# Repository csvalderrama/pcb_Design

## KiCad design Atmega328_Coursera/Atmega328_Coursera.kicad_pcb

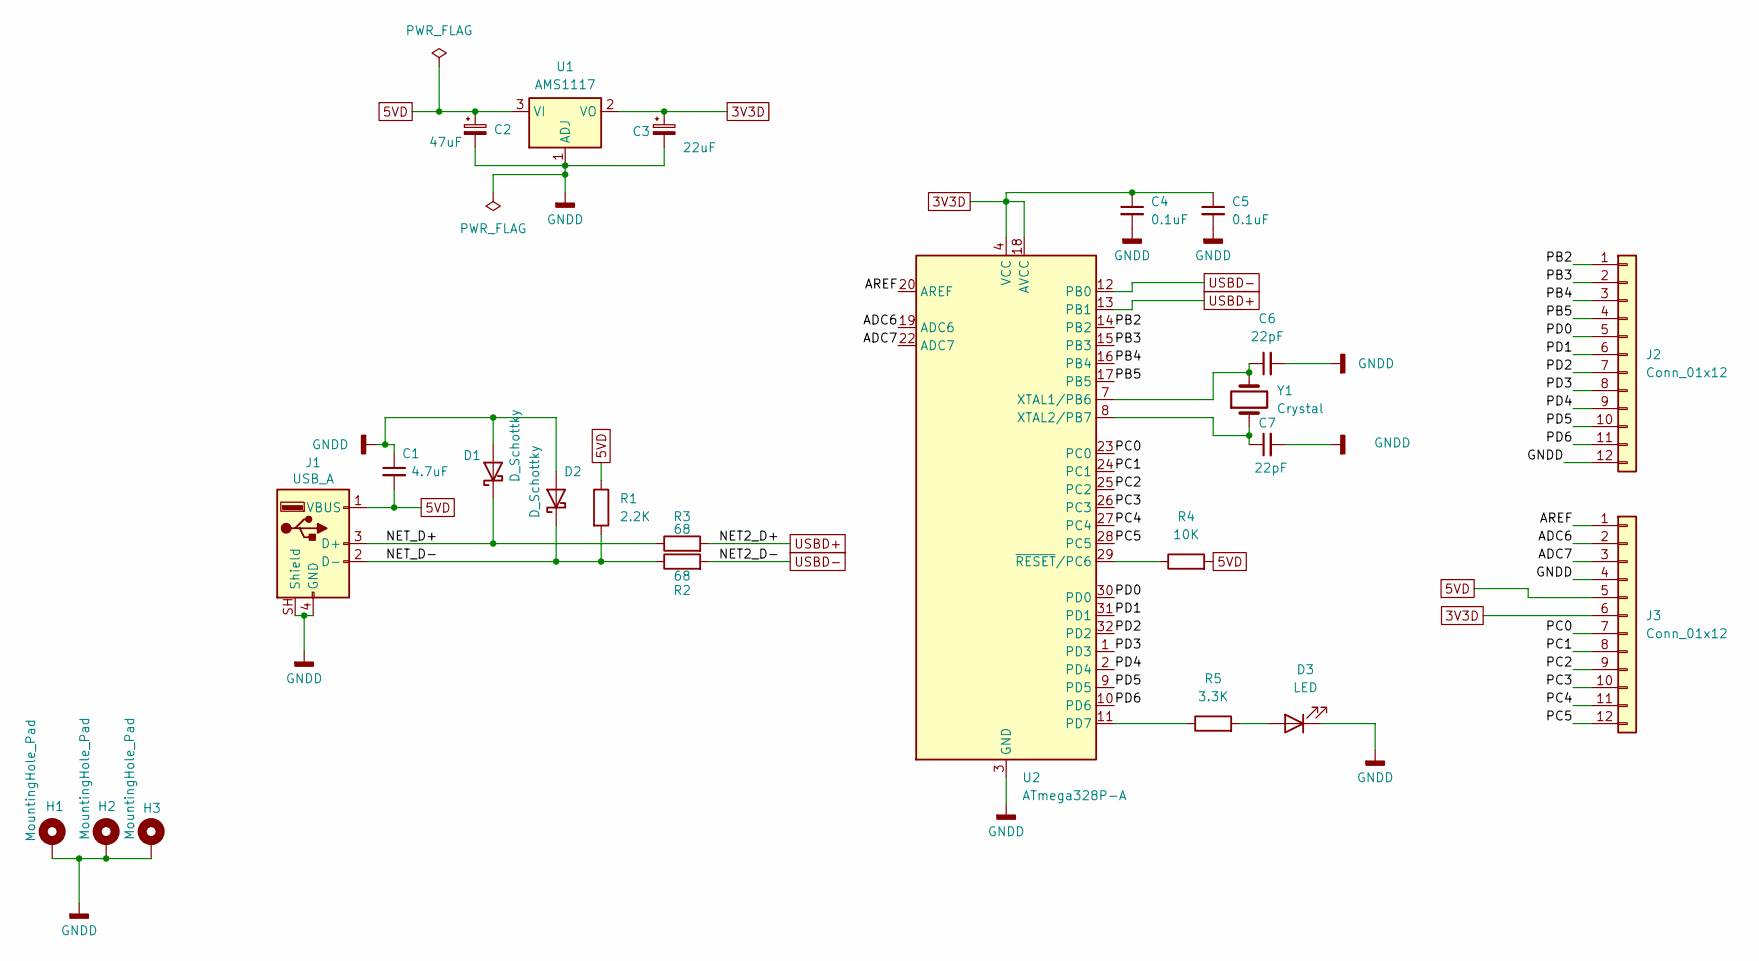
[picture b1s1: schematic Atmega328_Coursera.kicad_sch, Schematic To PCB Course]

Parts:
C1: 4.7uF; C_1206_3216Metric
C2: 47uF; C_1210_3225Metric
C3: 22uF; C_1210_3225Metric
C4, C5: 0.1uF; C_0805_2012Metric
C6, C7: 22pF; C_0805_2012Metric
D1, D2: D_Schottky; D_SMA
D3: LED; LED_D3.0mm
H1, H2, H3: MountingHole_Pad; MountingHole_3.2mm_M3_Pad_TopBottom
J1: USB_A; USB_A_TE_292303-7_Horizontal
J2: Conn_01x12; PinSocket_1x12_P2.54mm_Vertical
J3: Conn_01x12; PinHeader_1x12_P2.54mm_Vertical
R1: 2.2K; R_0805_2012Metric
R2, R3: 68; R_0805_2012Metric
R4: 10K; R_0805_2012Metric
R5: 3.3K; R_0805_2012Metric
U1: AMS1117; SOT-223-3_TabPin2
U2: ATmega328P-A; TQFP-32_7x7mm_P0.8mm
Y1: Crystal; Crystal_SMD_HC49-SD

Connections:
3V3D: C3.1, C4.1, C5.1, J3.6, U1.2 (VO), U2.4 (VCC), U2.6 (VCC), U2.18 (AVCC)
5VD: C1.2, C2.1, J1.1 (VBUS), J3.5, R1.1, R4.2, U1.3 (VI)
/ADC6: J3.2, U2.19 (ADC6)
/ADC7: J3.3, U2.22 (ADC7)
/AREF: J3.1, U2.20 (AREF)
/NET_D+: D1.1 (K), J1.3 (D+), R2.1
/NET_D-: D2.1 (K), J1.2 (D-), R1.2, R3.1
/PB2: J2.1, U2.14 (PB2)
/PB3: J2.2, U2.15 (PB3)
/PB4: J2.3, U2.16 (PB4)
/PB5: J2.4, U2.17 (PB5)
/PC0: J3.7, U2.23 (PC0)
/PC1: J3.8, U2.24 (PC1)
/PC2: J3.9, U2.25 (PC2)
/PC3: J3.10, U2.26 (PC3)
/PC4: J3.11, U2.27 (PC4)
/PC5: J3.12, U2.28 (PC5)
/PD0: J2.5, U2.30 (PD0)
/PD1: J2.6, U2.31 (PD1)
/PD2: J2.7, U2.32 (PD2)
/PD3: J2.8, U2.1 (PD3)
/PD4: J2.9, U2.2 (PD4)
/PD5: J2.10, U2.9 (PD5)
/PD6: J2.11, U2.10 (PD6)
GNDD: C1.1, C2.2, C3.2, C4.2, C5.2, C6.2, C7.2, D1.2 (A), D2.2 (A), D3.1 (K), H1.1 (1_1), H2.1 (1_1), H3.1 (1_1), J1.4 (GND), J1.SH (Shield), J2.12, J3.4, U1.1 (ADJ), U2.3 (GND), U2.5 (GND), U2.21 (GND)
unnamed: D3.2 (A), R5.2
unnamed: R5.1, U2.11 (PD7)
unnamed: C6.1, U2.7 (XTAL1/PB6), Y1.2
unnamed: C7.1, U2.8 (XTAL2/PB7), Y1.1
unnamed: R4.1, U2.29 (~RESET/PC6)
USBD+: R2.2, U2.13 (PB1)
USBD-: R3.2, U2.12 (PB0)

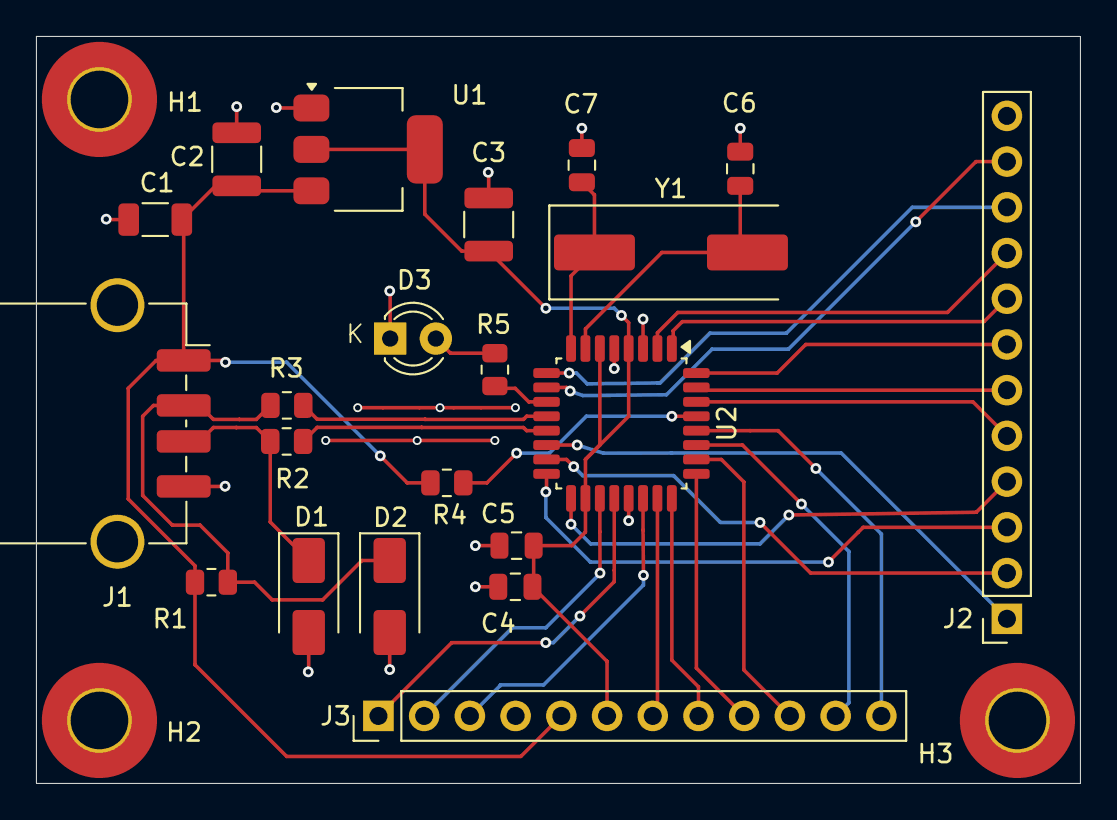
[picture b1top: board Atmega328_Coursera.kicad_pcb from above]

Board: 2 copper layers, 58.0 x 41.5 mm, 24 parts (0 on the bottom side), 32 nets.

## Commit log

2026-04-28 New repo PCB
2026-05-07 New updates and Optimization
2026-05-12 Add Guard Trace
